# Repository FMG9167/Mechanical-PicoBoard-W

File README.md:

# Mechanical-PicoBoard-W
A wireless mechanical keyboard made using raspberry pi pico W.
This keyboard has a split spacebar, in which the middle button acts as a function key. The function keys are switched from numbers to QWERASDFZXCV and on the right side, OP[ acts as mouse buttons.

While I was making my Hackpad (Macropad), I saw people making keyboards and I realized that I actually didnt knew how a mechanical keyboard works. So what better way to learn than to make one yourself!

# CAD

# PCB

# Firmware

For the Firmware, I used KMK with CircuitPy.

# BOM

1x Raspberyy Pi Pico W   - 599 inr <br>
70x Switches             - 1225 inr <br>
1x Keycap Set            - 2199 inr <br>
5x Stabilizers           - 500 inr <br>
1x Battery Holder        - 59 inr <br>
100x 1N4148 Diodes       - 99 inr <br>
5x PCB                   - 4320 inr <br>
40x Female Berg Strip    - 8.5 inr <br>
40x Male Berg Strip      - 6 inr <br>
M3x16mm Screw            - 0 inr <br>
Case                     - printing legion <br>

### TOTAL 9015.5 INR = 102.67 USD

With shipping it is 109.9 usd

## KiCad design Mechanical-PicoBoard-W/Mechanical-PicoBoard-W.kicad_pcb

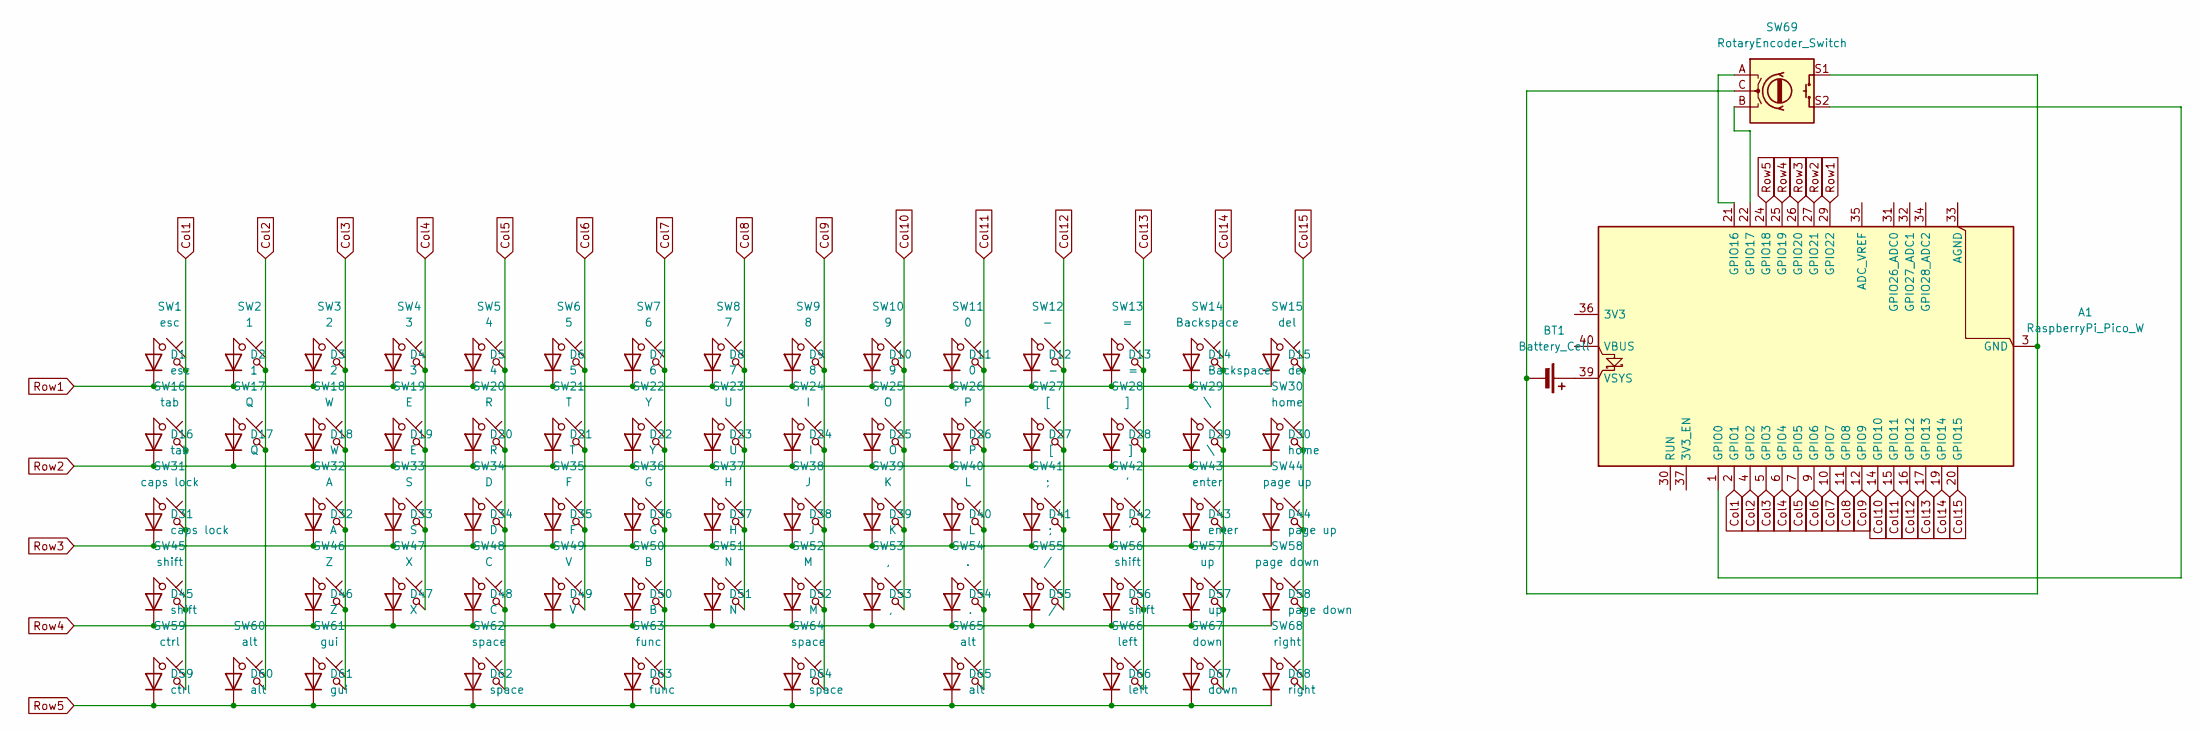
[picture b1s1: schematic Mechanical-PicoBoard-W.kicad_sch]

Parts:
A1: RaspberryPi_Pico_W; RaspberryPi_Pico_Common_THT_Model
BT1: Battery_Cell; BatteryHolder_Keystone_1042_1x18650
D1: esc; D_DO-35_SOD27_P7.62mm_Horizontal
D2: 1; D_DO-35_SOD27_P7.62mm_Horizontal
D3: 2; D_DO-35_SOD27_P7.62mm_Horizontal
D4: 3; D_DO-35_SOD27_P7.62mm_Horizontal
D5: 4; D_DO-35_SOD27_P7.62mm_Horizontal
D6: 5; D_DO-35_SOD27_P7.62mm_Horizontal
D7: 6; D_DO-35_SOD27_P7.62mm_Horizontal
D8: 7; D_DO-35_SOD27_P7.62mm_Horizontal
D9: 8; D_DO-35_SOD27_P7.62mm_Horizontal
D10: 9; D_DO-35_SOD27_P7.62mm_Horizontal
D11: 0; D_DO-35_SOD27_P7.62mm_Horizontal
D12: -; D_DO-35_SOD27_P7.62mm_Horizontal
D13: =; D_DO-35_SOD27_P7.62mm_Horizontal
D14: Backspace; D_DO-35_SOD27_P7.62mm_Horizontal
D15: del; D_DO-35_SOD27_P7.62mm_Horizontal
D16: tab; D_DO-35_SOD27_P7.62mm_Horizontal
D17: Q; D_DO-35_SOD27_P7.62mm_Horizontal
D18: W; D_DO-35_SOD27_P7.62mm_Horizontal
D19: E; D_DO-35_SOD27_P7.62mm_Horizontal
D20: R; D_DO-35_SOD27_P7.62mm_Horizontal
D21: T; D_DO-35_SOD27_P7.62mm_Horizontal
D22: Y; D_DO-35_SOD27_P7.62mm_Horizontal
D23: U; D_DO-35_SOD27_P7.62mm_Horizontal
D24: I; D_DO-35_SOD27_P7.62mm_Horizontal
D25: O; D_DO-35_SOD27_P7.62mm_Horizontal
D26: P; D_DO-35_SOD27_P7.62mm_Horizontal
D27: [; D_DO-35_SOD27_P7.62mm_Horizontal
D28: ]; D_DO-35_SOD27_P7.62mm_Horizontal
D29: \; D_DO-35_SOD27_P7.62mm_Horizontal
D30: home; D_DO-35_SOD27_P7.62mm_Horizontal
D31: caps lock; D_DO-35_SOD27_P7.62mm_Horizontal
D32: A; D_DO-35_SOD27_P7.62mm_Horizontal
D33: S; D_DO-35_SOD27_P7.62mm_Horizontal
D34: D; D_DO-35_SOD27_P7.62mm_Horizontal
D35: F; D_DO-35_SOD27_P7.62mm_Horizontal
D36: G; D_DO-35_SOD27_P7.62mm_Horizontal
D37: H; D_DO-35_SOD27_P7.62mm_Horizontal
D38: J; D_DO-35_SOD27_P7.62mm_Horizontal
D39: K; D_DO-35_SOD27_P7.62mm_Horizontal
D40: L; D_DO-35_SOD27_P7.62mm_Horizontal
D41: ;; D_DO-35_SOD27_P7.62mm_Horizontal
D42: '; D_DO-35_SOD27_P7.62mm_Horizontal
D43: enter; D_DO-35_SOD27_P7.62mm_Horizontal
D44: page up; D_DO-35_SOD27_P7.62mm_Horizontal
D45, D56: shift; D_DO-35_SOD27_P7.62mm_Horizontal
D46: Z; D_DO-35_SOD27_P7.62mm_Horizontal
D47: X; D_DO-35_SOD27_P7.62mm_Horizontal
D48: C; D_DO-35_SOD27_P7.62mm_Horizontal
D49: V; D_DO-35_SOD27_P7.62mm_Horizontal
D50: B; D_DO-35_SOD27_P7.62mm_Horizontal
D51: N; D_DO-35_SOD27_P7.62mm_Horizontal
D52: M; D_DO-35_SOD27_P7.62mm_Horizontal
D53: ,; D_DO-35_SOD27_P7.62mm_Horizontal
D54: .; D_DO-35_SOD27_P7.62mm_Horizontal
D55: /; D_DO-35_SOD27_P7.62mm_Horizontal
D57: up; D_DO-35_SOD27_P7.62mm_Horizontal
D58: page down; D_DO-35_SOD27_P7.62mm_Horizontal
D59: ctrl; D_DO-35_SOD27_P7.62mm_Horizontal
D60, D65: alt; D_DO-35_SOD27_P7.62mm_Horizontal
D61: gui; D_DO-35_SOD27_P7.62mm_Horizontal
D62, D64: space; D_DO-35_SOD27_P7.62mm_Horizontal
D63: func; D_DO-35_SOD27_P7.62mm_Horizontal
D66: left; D_DO-35_SOD27_P7.62mm_Horizontal
D67: down; D_DO-35_SOD27_P7.62mm_Horizontal
D68: right; D_DO-35_SOD27_P7.62mm_Horizontal
SW1: esc; SW_Cherry_MX_1.00u_PCB
SW2: 1; SW_Cherry_MX_1.00u_PCB
SW3: 2; SW_Cherry_MX_1.00u_PCB
SW4: 3; SW_Cherry_MX_1.00u_PCB
SW5: 4; SW_Cherry_MX_1.00u_PCB
SW6: 5; SW_Cherry_MX_1.00u_PCB
SW7: 6; SW_Cherry_MX_1.00u_PCB
SW8: 7; SW_Cherry_MX_1.00u_PCB
SW9: 8; SW_Cherry_MX_1.00u_PCB
SW10: 9; SW_Cherry_MX_1.00u_PCB
SW11: 0; SW_Cherry_MX_1.00u_PCB
SW12: -; SW_Cherry_MX_1.00u_PCB
SW13: =; SW_Cherry_MX_1.00u_PCB
SW14: Backspace; SW_Cherry_MX_2.00u_PCB
SW15: del; SW_Cherry_MX_1.00u_PCB
SW16: tab; SW_Cherry_MX_1.50u_PCB
SW17: Q; SW_Cherry_MX_1.00u_PCB
SW18: W; SW_Cherry_MX_1.00u_PCB
SW19: E; SW_Cherry_MX_1.00u_PCB
SW20: R; SW_Cherry_MX_1.00u_PCB
SW21: T; SW_Cherry_MX_1.00u_PCB
SW22: Y; SW_Cherry_MX_1.00u_PCB
SW23: U; SW_Cherry_MX_1.00u_PCB
SW24: I; SW_Cherry_MX_1.00u_PCB
SW25: O; SW_Cherry_MX_1.00u_PCB
SW26: P; SW_Cherry_MX_1.00u_PCB
SW27: [; SW_Cherry_MX_1.00u_PCB
SW28: ]; SW_Cherry_MX_1.00u_PCB
SW29: \; SW_Cherry_MX_1.50u_PCB
SW30: home; SW_Cherry_MX_1.00u_PCB
SW31: caps lock; SW_Cherry_MX_1.75u_PCB
SW32: A; SW_Cherry_MX_1.00u_PCB
SW33: S; SW_Cherry_MX_1.00u_PCB
SW34: D; SW_Cherry_MX_1.00u_PCB
SW35: F; SW_Cherry_MX_1.00u_PCB
SW36: G; SW_Cherry_MX_1.00u_PCB
SW37: H; SW_Cherry_MX_1.00u_PCB
SW38: J; SW_Cherry_MX_1.00u_PCB
SW39: K; SW_Cherry_MX_1.00u_PCB
SW40: L; SW_Cherry_MX_1.00u_PCB
SW41: ;; SW_Cherry_MX_1.00u_PCB
SW42: '; SW_Cherry_MX_1.00u_PCB
SW43: enter; SW_Cherry_MX_2.25u_PCB
SW44: page up; SW_Cherry_MX_1.00u_PCB
SW45: shift; SW_Cherry_MX_2.25u_PCB
SW46: Z; SW_Cherry_MX_1.00u_PCB
SW47: X; SW_Cherry_MX_1.00u_PCB
SW48: C; SW_Cherry_MX_1.00u_PCB
SW49: V; SW_Cherry_MX_1.00u_PCB
SW50: B; SW_Cherry_MX_1.00u_PCB
SW51: N; SW_Cherry_MX_1.00u_PCB
SW52: M; SW_Cherry_MX_1.00u_PCB
SW53: ,; SW_Cherry_MX_1.00u_PCB
SW54: .; SW_Cherry_MX_1.00u_PCB
SW55: /; SW_Cherry_MX_1.00u_PCB
SW56: shift; SW_Cherry_MX_1.75u_PCB
SW57: up; SW_Cherry_MX_1.00u_PCB
SW58: page down; SW_Cherry_MX_1.00u_PCB
SW59: ctrl; SW_Cherry_MX_1.25u_PCB
SW60: alt; SW_Cherry_MX_1.25u_PCB
SW61: gui; SW_Cherry_MX_1.25u_PCB
SW62, SW64: space; SW_Cherry_MX_2.25u_PCB
SW63: func; SW_Cherry_MX_1.75u_PCB
SW65: alt; SW_Cherry_MX_1.00u_PCB
SW66: left; SW_Cherry_MX_1.00u_PCB
SW67: down; SW_Cherry_MX_1.00u_PCB
SW68: right; SW_Cherry_MX_1.00u_PCB
SW69: RotaryEncoder_Switch; RotaryEncoder_Alps_EC11E-Switch_Vertical_H20mm_Model

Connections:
Col1: A1.2 (GPIO1), SW1.2, SW16.2, SW31.2, SW45.2, SW59.2
Col2: A1.4 (GPIO2), SW2.2, SW17.2, SW60.2
Col3: A1.5 (GPIO3), SW3.2, SW18.2, SW32.2, SW46.2, SW61.2
Col4: A1.6 (GPIO4), SW4.2, SW19.2, SW33.2, SW47.2
Col5: A1.7 (GPIO5), SW5.2, SW20.2, SW34.2, SW48.2, SW62.2
Col6: A1.9 (GPIO6), SW6.2, SW21.2, SW35.2, SW49.2
Col7: A1.10 (GPIO7), SW7.2, SW22.2, SW36.2, SW50.2, SW63.2
Col8: A1.11 (GPIO8), SW8.2, SW23.2, SW37.2, SW51.2
Col9: A1.12 (GPIO9), SW9.2, SW24.2, SW38.2, SW52.2, SW64.2
Col10: A1.14 (GPIO10), SW10.2, SW25.2, SW39.2, SW53.2
Col11: A1.15 (GPIO11), SW11.2, SW26.2, SW40.2, SW54.2, SW65.2
Col12: A1.16 (GPIO12), SW12.2, SW27.2, SW41.2, SW55.2
Col13: A1.17 (GPIO13), SW13.2, SW28.2, SW42.2, SW56.2, SW66.2
Col14: A1.19 (GPIO14), SW14.2, SW29.2, SW43.2, SW57.2, SW67.2
Col15: A1.20 (GPIO15), SW15.2, SW30.2, SW44.2, SW58.2, SW68.2
unnamed: A1.1 (GPIO0), SW69.S2
unnamed: A1.21 (GPIO16), SW69.A
unnamed: A1.22 (GPIO17), SW69.B
unnamed: A1.39 (VSYS), BT1.1 (+)
unnamed: A1.3 (GND), A1.8 (GND), A1.13 (GND), A1.18 (GND), A1.23 (GND), A1.28 (GND), A1.38 (GND), BT1.2 (-), SW69.C, SW69.S1
unnamed: D1.2 (A), SW1.1
unnamed: D2.2 (A), SW2.1
unnamed: D3.2 (A), SW3.1
unnamed: D4.2 (A), SW4.1
unnamed: D5.2 (A), SW5.1
unnamed: D6.2 (A), SW6.1
unnamed: D7.2 (A), SW7.1
unnamed: D8.2 (A), SW8.1
unnamed: D9.2 (A), SW9.1
unnamed: D10.2 (A), SW10.1
unnamed: D11.2 (A), SW11.1
unnamed: D12.2 (A), SW12.1
unnamed: D13.2 (A), SW13.1
unnamed: D14.2 (A), SW14.1
unnamed: D15.2 (A), SW15.1
unnamed: D16.2 (A), SW16.1
unnamed: D17.2 (A), SW17.1
unnamed: D18.2 (A), SW18.1
unnamed: D19.2 (A), SW19.1
unnamed: D20.2 (A), SW20.1
unnamed: D21.2 (A), SW21.1
unnamed: D22.2 (A), SW22.1
unnamed: D23.2 (A), SW23.1
unnamed: D24.2 (A), SW24.1
unnamed: D25.2 (A), SW25.1
unnamed: D26.2 (A), SW26.1
unnamed: D27.2 (A), SW27.1
unnamed: D28.2 (A), SW28.1
unnamed: D29.2 (A), SW29.1
unnamed: D30.2 (A), SW30.1
unnamed: D31.2 (A), SW31.1
unnamed: D32.2 (A), SW32.1
unnamed: D33.2 (A), SW33.1
unnamed: D34.2 (A), SW34.1
unnamed: D35.2 (A), SW35.1
unnamed: D36.2 (A), SW36.1
unnamed: D37.2 (A), SW37.1
unnamed: D38.2 (A), SW38.1
unnamed: D39.2 (A), SW39.1
unnamed: D40.2 (A), SW40.1
unnamed: D41.2 (A), SW41.1
unnamed: D42.2 (A), SW42.1
unnamed: D43.2 (A), SW43.1
unnamed: D44.2 (A), SW44.1
unnamed: D45.2 (A), SW45.1
unnamed: D46.2 (A), SW46.1
unnamed: D47.2 (A), SW47.1
unnamed: D48.2 (A), SW48.1
unnamed: D49.2 (A), SW49.1
unnamed: D50.2 (A), SW50.1
unnamed: D51.2 (A), SW51.1
unnamed: D52.2 (A), SW52.1
unnamed: D53.2 (A), SW53.1
unnamed: D54.2 (A), SW54.1
unnamed: D55.2 (A), SW55.1
unnamed: D56.2 (A), SW56.1
unnamed: D57.2 (A), SW57.1
unnamed: D58.2 (A), SW58.1
unnamed: D59.2 (A), SW59.1
unnamed: D60.2 (A), SW60.1
unnamed: D61.2 (A), SW61.1
unnamed: D62.2 (A), SW62.1
unnamed: D63.2 (A), SW63.1
unnamed: D64.2 (A), SW64.1
unnamed: D65.2 (A), SW65.1
unnamed: D66.2 (A), SW66.1
unnamed: D67.2 (A), SW67.1
unnamed: D68.2 (A), SW68.1
Row1: A1.29 (GPIO22), D1.1 (K), D2.1 (K), D3.1 (K), D4.1 (K), D5.1 (K), D6.1 (K), D7.1 (K), D8.1 (K), D9.1 (K), D10.1 (K), D11.1 (K), D12.1 (K), D13.1 (K), D14.1 (K), D15.1 (K)
Row2: A1.27 (GPIO21), D16.1 (K), D17.1 (K), D18.1 (K), D19.1 (K), D20.1 (K), D21.1 (K), D22.1 (K), D23.1 (K), D24.1 (K), D25.1 (K), D26.1 (K), D27.1 (K), D28.1 (K), D29.1 (K), D30.1 (K)
Row3: A1.26 (GPIO20), D31.1 (K), D32.1 (K), D33.1 (K), D34.1 (K), D35.1 (K), D36.1 (K), D37.1 (K), D38.1 (K), D39.1 (K), D40.1 (K), D41.1 (K), D42.1 (K), D43.1 (K), D44.1 (K)
Row4: A1.25 (GPIO19), D45.1 (K), D46.1 (K), D47.1 (K), D48.1 (K), D49.1 (K), D50.1 (K), D51.1 (K), D52.1 (K), D53.1 (K), D54.1 (K), D55.1 (K), D56.1 (K), D57.1 (K), D58.1 (K)
Row5: A1.24 (GPIO18), D59.1 (K), D60.1 (K), D61.1 (K), D62.1 (K), D63.1 (K), D64.1 (K), D65.1 (K), D66.1 (K), D67.1 (K), D68.1 (K)

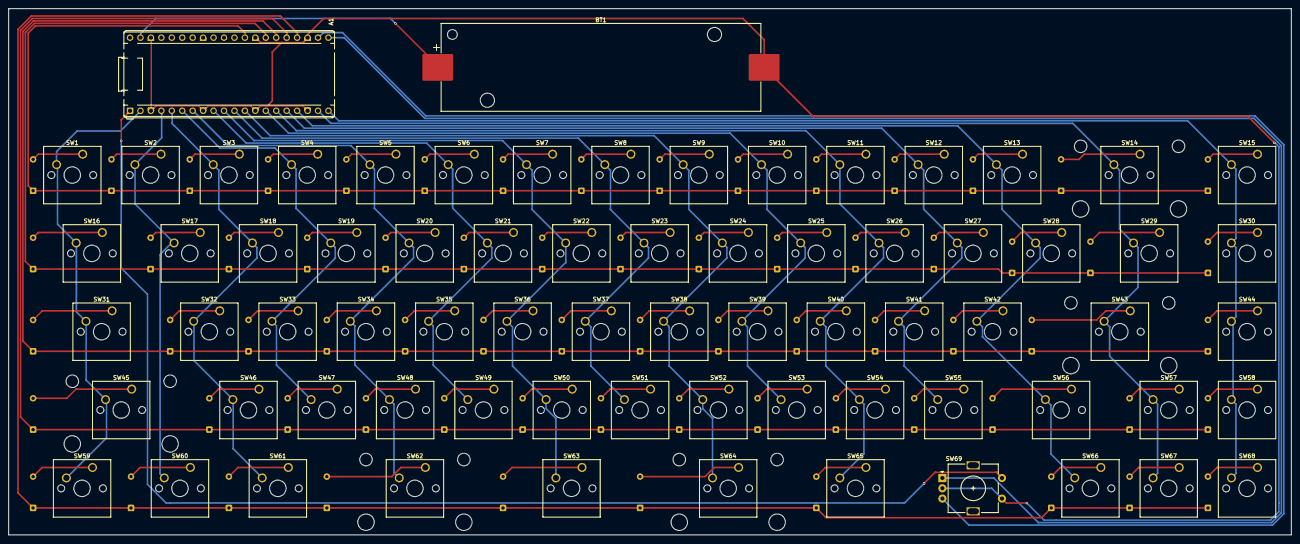
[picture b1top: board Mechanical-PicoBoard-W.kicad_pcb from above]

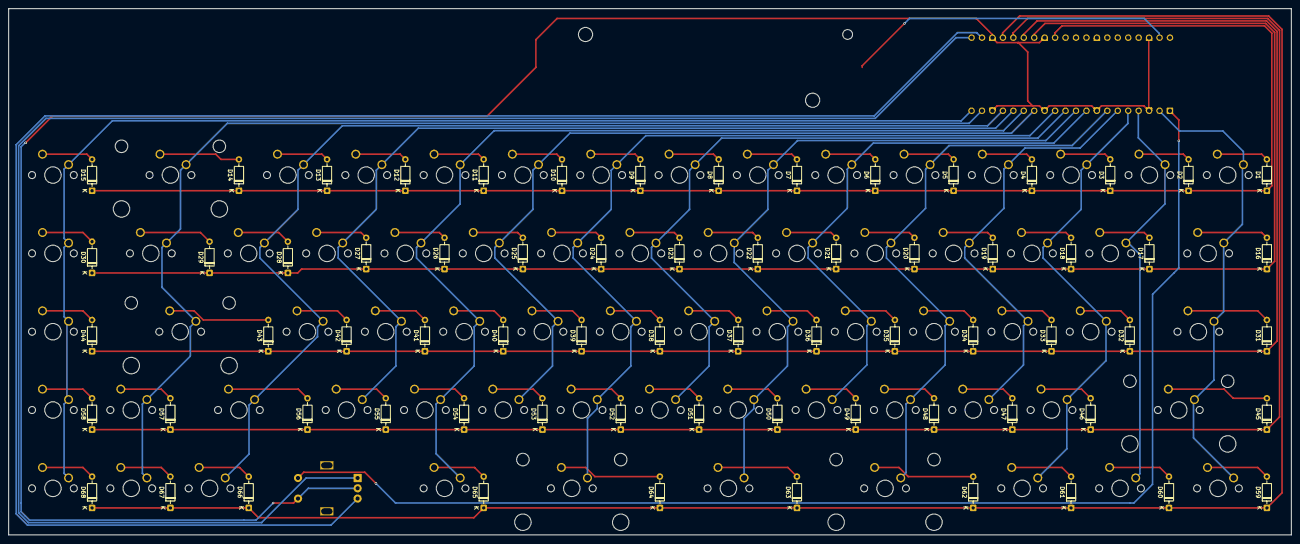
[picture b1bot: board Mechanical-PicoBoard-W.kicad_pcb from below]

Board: 2 copper layers, 312.0 x 128.0 mm, 139 parts (68 on the bottom side), 93 nets.

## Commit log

2025-06-28 day one
2025-06-29 day two
2025-06-30 day three
2025-07-05 fixed one image error
2025-07-05 yet another fix T-T
2025-07-06 started cad
2025-07-16 the sad day
2025-07-19 recovery day
2025-07-22 Finished
2025-07-22 Arranged Folders
2025-07-22 Forgot about this
2025-07-23 Added step cad files
2025-07-24 Added incline
2025-07-24 added case to bom
2025-07-24 added a leftover comma
2025-07-29 Added screws to bom
2025-08-02 made the case not so simple
2025-08-15 Added update to the case
2025-09-15 updated pricing and fixed gerbers
2025-09-15 Updated journal and readme
2025-09-17 i forgot about stabilizers :(
